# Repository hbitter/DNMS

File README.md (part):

## [English text below](#dnms-digital-noise-measurement-sensor-english)

## DNMS (Digital Noise Measurement Sensor)

Ein Sensor-Modul zur Schallpegelmessung. Es wird neben dem LAeq-Wert über einem Zeitintervall auch der min. und max. LA-Wert in diesem Zeitintervall festgehalten. Das zentrale Element des DNMS ist ein digitales MEMS-Mikrofon (InvenSense ICS-43434). Ein Mikrocontroller-Board (Teensy3.6 / Teensy4.0) übernimmt die digitalen Daten vom Mikrofon über die I²S Schnittstelle als  24-Bit, 44,1 kHz PCM Daten (ab Firmware Version 2 - zuvor nur 16-Bit).  Die Audiodaten werden über einen digitalen A-Filter bewertet, dann wird der Effektivwert bestimmt und daraus der Schalldruckpegel entsprechend der Mikrofonsensitivität berechnet. Die einzelnen Schalldruckpegelwerte werden zu einem fortlaufenden LAeq-Wert weitergerechnet. Ebenso werden der max. und min. Schalldruckpegel (LAmax, LAmin) aus dem Intervall abgespeichert.

Die Werte werden dann über eine I²C-Schnittstelle an einen abfragenden Mikrocontroller zur Weiterverarbeitung übertragen. Das Abfrage-Intervall kann 1 Sekunde betragen oder auch bis zu 3600 Sekunden.

Eine Version mit der Möglichkeit das Frequenzspektrum zu betrachten ist seit einiger Zeit verfügbar. Terzwerte von 20Hz - 20000Hz können ausgegeben werden. Terzwerte werden z.Zt. nicht von Sensor.Community unterstützt, deshalb gibt es spezielle Versionen der NodeMCU Firmware um Terzwerte auf der lokalen Webseite der NodeMCU auszugeben und an weitere APIs wie z.B. zu einer InfluxDB zu senden.

Mit der Firmware Version 5 für Teensy4.0 werden nun auch Z-Werte (LZeq, LZmin, LZmax sowie Z-Terzwerte) unterstützt.

### Bei der Firma Watterott electronic GmbH kann nun das Mikrofon IM72D128 von Infineon fertig in einem Kunststoffrohr eingegossen im Shop bestellt werden (https://shop.watterott.com/Mikrofon-IM72D128V01-im-127mm-Rundrohr). Das IM72D128 Mikrofon auf einer Platine und mit Anschlusskabel aber nicht  im Kunststoffrohr eingegossen ist ebenfalls verfügbar (https://shop.watterott.com/Mikrofon-IM72D128V01-Platine-mit-Anschlussleitung).
 
## Neuigkeiten

### Oktober 2026

- Neue Teensy4.0 Firmware DNMS_V6.0.x für IM72D128 und ICS-43434 Mikrofone.   
 	+ Komplettes Refactoring der Firmware mit Optimierung der Verwendung von Double (nur noch wenn absolut notwendig), dadurch erfordert die Berechnung der Leq Werte deutlich weniger Ressourcen.
 	+  Fehlerbeseitigung einer Race-Condition zwischen 1. und 2. Messintervall.
 	+  Die Parameterwerte zur Frequenzgangkorrektur sind nicht mehr in der Firmware fest abgespeichert. Es werden für jeden Mikrofontyp 31 Korrekturwerte vom Kommunikationsprozessor an die Teensy Firmware beim Start übertragen, daraus berechnet die Teensy Firmware die Korrekturwerte für den gewählten Mikrofontyp für die FFT Bins.
 	+  Änderung der Filterparameter für die I²C Kommunikation zwischen Teensy und Kommunikationsprozessor, dadurch stabilere I²C Übertragung. Beim Kompilieren der Firmware ist es deshalb notwendig die angepasste teensy4_i2c-master Library zu benutzen (zu finden unter Firmware/Teensy/Teensy4.0/).

 	<mark>Achtung: Um diese Firmware zu nutzen, ist die Firmware Version airrohr-DNMS-6.0.0 (oder höher) beim NodeMCU Kommunikationsprozessor oder beim Raspberry Pi  die Version dnms-0.9.27 bzw. dnms-0.9.28 (oder höher) notwendig. Nur diese Versionen haben die Parameter zur Frequenzgangkorrektur abgespeichert und übertragen diese Werte beim Start.<mark>
 	
- Neue NodeMCU Firmware AIRROHR-DNMS-6.0, AIRROHR-DNMS-6.0-en, AIRROHR-DNMS-6.0-fr
	+ Unterstützung der Teensy4.0 Firmware DNMS_V6.0.x mit der wesentlichen Änderung, dass die Frequenzgangkorrekturwerte beim Start von der NodeMCU an die Teensy4.0 Firmware übertragen werden. Ist eine ältere Firmware auf dem Tennsy4.0 Board installiert, so wird dies ebenfalls unterstützt d.h. es ist abwärtskompatibel.
	+ Neue Farbe und neues Logo für den lokalen Webserver:
	 
	+ Verbessertes Handling der Datenübertragung zu Sensor.Community und zu MQTT-Brokern um Datenverlust bei der Übertragung weiter zu reduzieren.
	
	+  Möglichkeit die NodeMCU Firmware direkt über den Webbrowser auf einen ESP8266  zu flashen. Dies ist möglich mit allen Webbrowsern, die das Web Serial API unterstützen (Chrome, Edge, Brave, Opera aber nicht Firefox ). Um die Funktion zu benutzen,  den entsprechenden Link aufrufen abhängig von der gewünschten Sprachversion:	
		+ Webflasher Deutsche Firmware: https://hbitter.github.io/DNMS/flash-de.html
		+ Webflasher Englische Firmware: https://hbitter.github.io/DNMS/flash-en.html
		+ Webflasher Französische Firmware: https://hbitter.github.io/DNMS/flash-fr.html

- Raspberry Pi Firmware Versionen dnms-0.9.27 und dnms-0.9.28
	+ Die Version dnms-0.9.28 enthält  im Unterschied zur Version dnms-0.9.27 einen lokalen Webserver, der Sztatus Informationen anzeigt und über den die Konfiguration des Sensors angesehen und geändert werden kann. Weiterhin bietet die Version dnms-0.9.28 ein HTTP API (POST) für die Daten des 1. Messintervalls.
	+ Unterstützung der Teensy4.0 Firmware DNMS_V6.0.x mit der wesentlichen Änderung, dass die Frequenzgangkorrekturwerte beim Start vom Raspberry Pi  an die Teensy4.0 Firmware übertragen werden. Ist eine ältere Firmware auf dem Tennsy4.0 Board installiert, so wird dies ebenfalls unterstützt d.h. es ist abwärtskompatibel.
	+ Lokaler Webserver der Version dnms-0.9.28 mit Farbe und Logo entsprechend der NodeMCU Version.

### Mai 2026

- Neues Teensy 4.0 Board DNMS-T4.0-V1.8S mit Layout für SMD Bestückung , so dass nicht nur die Herstellung der Platine beauftragt werden kann sondern direkt die Bestückung bei Firmen wie Aisler, EuroCircuits, JLCPCB oder PCBWay und weiteren. Das Einlöten des Teensy Boards sollte aus Kosten- und Logistikgründen allerdings weiterhin selbst erfolgen. Zwei Bauteilelisten sind als Beispiel für die Bestellung fertig bestückter Boards beigefügt. Dies ist jedoch immer den aktuell lieferbaren Bauelementen anzupassen. Das Layout basiert auf der EasyEDA Vorlage von Ralf Bötticher (vielen Dank!). Weiterhin gibt es zwei Änderungen im Layout:
	+ Verzicht der Brücke J1,  die Brücke war zur Stromversorgung für das standalone Flashen des Boards. Eine Auftrennung der Verbindung VIN - VUSB auf dem Teensy 4.0 Board ist nicht mehr notwendig.
	+ Einfügung einer Sicherung F1 in die 5V Versorgungsleitung der extended I²C Verbindung d.h. zwischen Kommunikationsprozessor und Teensy 4.0 Board.

 - Neue Raspberry Pi Firmware dnms-0.9.25 mit folgenden Verbesserungen:
	+ Möglichkeit C-Werte abzufragen und weiterzugeben, dazu ist die Teensy 4.0 Version DNMS_V5.9.x Voraussetzung. Abhängig von der Menge der übertragenen Daten zwischen Teensy und Raspberry Pi  wird empfohlen die I²C Übertragungsrate von 100 kHz auf 200 kHz zu erhöhen (`dtparam=i2c_arm=on,i2c_arm_baudrate=20000` in der Datei `/boot/firmware/config.txt`).
	+ In der Konfigurationsdatei dnms.conf können nun wieder die Bool Werte mit true und false angegeben werden.

- Neue Teensy 4.0 Firmware DNMS_V5.9.x  für IM72D128 und ICS-43434 Mikrofone mit dem Unterschied zur Version DNMS_V5.8.x, dass zusätzlich C-Werte berechnet und abgerufen werden können. Wenn keine C-Werte benötigt werden, ist die Version  DNMS_V5.8.x weiterhin aktuell. Eine Version mit Abfrage der C-Werte ist die Raspberry Pi Version dnms-0.9.25. Eine Abfrage der C-Werte für die NodeMCU Firmware ist z.Zt. nicht geplant.

- Neue NodeMCU Firmware AIRROHR-DNMS-5.17, AIRROHR-DNMS-5.17-en, AIRROHR-DNMS-5.17-fr
	+ Neue Konfigurationsmöglichkeit für verschiedene Mikrofone und Frequenzgangkorrekturen der Mikrofone. Eine Teensy4.0 Version ab DNMS_V5.8.x ist Voraussetzung um dies zu nutzen.
	+ Konfiguration eines digitalen Eingangs an der der NodeMCU. Der Zustand wird mit der Bezeichnung  DIN01 zur InfluxDB übertragen.
	+ Kleine Korrekturen im Source Code, so dass in der Arduino IDE Version 2.3.8 die Übersetzung ohne Warnungen erfolgt.

- Neue Teensy 4.0 Firmware DNMS_V5.8.x  für IM72D128 und ICS-43434 Mikrofone mit:
	+ zusätzlicher Auswahl der Frequenzgangkorrektur für das DLR Gehäuse mit IM72D128 Mikrofon, sowie Auswahl ohne Frequenzgangkorrektur für IM72D128 und ICS-43434 Mikrofon.
	+ Kleine Korrekturen im Source Code, so dass in der Arduino IDE Version 2.3.8 die Übersetzung ohne Warnungen erfolgt. Dies betrifft auch die Library dnms_audio_lib-master.zip, deshalb beim Übersetzen die veränderte Library einbinden.
	+ Korrekturen an der I²C Übertragung, Änderung der Werte für die Glitch Filter von SDA und SCL im Slave Modus. Diese Korrekturen befinden sich in der Library  teensy4_i2c-master.zip, deshalb beim Übersetzen die veränderte Library einbinden.

### Mai 2025

- Neues Testprogramm für Teensy4.0 Board und angeschlossenem Mikrofon ICS-43434:  DNMS_Vt.8.4 und für Mikrofon IM72D128: DNMS_Vt.8.6, mit verbesserter Frequenzgangkorrektur

- Neue Teensy 4.0 Firmware DNMS_V5.5.x  für IM72D128 und ICS-43434 Mikrofone mit:
	+ Verbesserte Korrektur des Frequenzgangs für IM72D128 Mikrofon und ICS-43434 Mikrofon. Dies verbessert auch die Terzwerte des Spektrums.

 - Neue Raspberry Pi Firmware dnms-0.9.23 ersetzt dnms-0.9.21 aufgrund von Fehlern:
	 + Bei der Umwandlung der MAC-Adresse in die ID
	 + Entfernung Testausgabe der Daten auf Konsole bei Sensor.Community Übertragung
	 + Beseitigung Pufferüberlauf für InfluxDB/MQTT Übertragung, wenn keine Übertragung konfiguriert war

### Oktober 2024

- Neue NodeMCU Firmware AIRROHR-DNMS-5.16 mit:
	+ Neue Konfigurationsmöglichkeit die WLAN Verbindung ohne Passwort auszuwählen aufgrund einer Änderung in der Wifi Lib. Dies ist notwendig  z.B. für Freifunk WLAN Verbindungen.
	+ Verbesserte Fehlerbehandlung bei der Datenübertragung und entsprechende Fehlerausgaben.
	+ Fehlerbeseitigung bei der Übertragung des Zeitstempels zur InfluxDB und zu einem MQTT Broker, wenn der DNMS Sensor nicht konfiguriert ist.

### September 2024

 - Raspberry Pi dnms-0.9.21 ersetzt Version dnms-0.9.20 aufgrund von Fehlern.
 	+ Fehler in der dnms.conf beim Eintrag 'mqtt_transmit'.
 	+ Fehlerhaft gesetzte Prioritäten für die Threads in der dnms.conf ('prio_1st_timer', ... usw).
 	+ Neben der InfluxDB HTTP Übertragung kann nun parallel eine Übertragung der Werte zu einem MQTT Broker erfolgen.
 		
 - Raspberry Pi dnms-0.9.20 Version mit folgenden neuen Funktionen:
	+ Data Logging der Messwerte auf der SD-Karte des Raspberry Pi
	+ Externer Start und Stop der Messwertübertragung, Ausgabe und Speicherung mittels einer named pipe
	+ Änderung der Eingabe von Bool-Werten in der Konfigurationsdatei dnms.conf: Für false eine '0' und für true eine '1' eingeben.

 - Möglichkeit die NodeMCU Firmware direkt über den Webbrowser auf einen ESP8266  zu flashen. Dies ist möglich mit allen Webbrowsern, die das Web Serial API unterstützen (Chrome, Edge, Brave, Opera aber nicht Firefox ). Um die Funktion zu benutzen,  den entsprechenden Link aufrufen abhängig von der gewünschten Sprachversion:
	+ Deutsche Firmware: https://hbitter.github.io/DNMS/flash-de.html
	+ Englische Firmware: https://hbitter.github.io/DNMS/flash-en.html
	+ Französische Firmware: https://hbitter.github.io/DNMS/flash-fr.html

### Juli 2024

- Neue Firmware für Teensy4.0 DNMS_V5.4.x - für ICS-43434 und IM72D128 Mikrofon
	+ Ersetzt DNMS_V5.3.x da in der Version DNMS_V5.3.x Fehler in der Berechnung der Terzwerte waren. DNMS_V5.3.x bitte ersetzen mit DNMS_V5.4.x 
	
- Neue NodeMCU Firmware AIRROHR-DNMS-5.12 mit:
	+ NTP Server können nun in der Konfiguration gesetzt werden unter "Weitere Einstellungen"
	+ Konfigurationsänderung für die Übertragung zum MQTT Broker, eigenes Feld für die Konfiguration der MQTT Messung. Dies wird im InfluxDB Line Protocol als Measurement weitergegeben

 - Raspberry Pi dnms-0.9.18 Fehlerkorrektur und neue Funktion:
	 - Korrektur eines Fehlers: Wenn nur die Ausgabe auf dem Terminal konfiguriert war, wurden die Werte nicht richtig auf dem Terminal ausgegeben.
 	- Neue Möglichkeit der Weitergabe von Messwerten mittels einer named pipe (oder auch fifo) zu anderen Anwendungen auf dem Raspberry Pi.

### Juni 2024

 - Raspberry Pi dnms-0.9.16 Korrektur der Versionsnummer:
	 - Die Versionsnummer wurde falsch (0.9.15 statt 0.9.16) angezeigt
 - Neue NodeMCU Firmware AIRROHR-DNMS-5.8 mit:
	 - MQTT Übertragung (z.Zt. kein TLS)
	 - Unterstützung der neuen Teensy4.0 Firmware DNMS_V5.3.x (Mikrofone ICS-43434 und IM72D128 in einer Teensy4 Firmware)
	 - Möglichkeit nach Restart mit den Messungen zur vollen Minute oder zur vollen Stunde zu beginnen<br>
	 
	 Weitere Details dazu im README.md unter Firmware/NodeMCU.

 - Erweiterte Raspberry Pi Anwendung dnms-0.9.16 mit:
	 - MQTT Übertragung zu einem MQTT-Broker (z.Zt. kein TLS)
	 - Unterstützung der neuen Teensy4.0 Firmware DNMS_V5.3.x (Mikrofone ICS-43434 und IM72D128 in einer Teensy4 Firmware)
	 - Einführung eines DNMS Korrekturwertes für die Lärmwerte (nicht für Frequenzspektren) entsprechend der NodeMCU Firmware  <br>
	 
	 Weitere Details dazu im README.md unter Firmware/Raspberry Pi.
	 
 - Neue Teensy4.0 Firmware DNMS_V5.3.x mit:
	 - Zusammenführung der bisher getrennten Versionen für die beiden Mikrofone ICS-43434 und IM72D128 in einer Teensy4.0 Firmware. Die Auswahl des Mikrofons erfolgt über die Konfiguration in der NodeMCU bzw. im Raspberry Pi und wird mittels Umschaltbefehl an die Teensy4.0 Firmware übertragen. Wird kein Umschaltbefehl übertragen ist als standardmäßig das ICS-43434 ausgewählt d.h. auch ältere NodeMCU Firmware unterstützt die Version DNMS_V5.3.x mit ICS-43434 Mikrofon. <br>

	 Weitere Details dazu im README.md unter Firmware/Teensy4.0/V5.	 

### April 2024
 - Neue NodeMCU Firmware NRZ-2020-134-DNMS-5.6 mit:
	 - Fehlerbeseitigung für DNMS Korrekturwert (Issue #54)
	 - LED Statusanzeige
	 - geänderte Speicheraufteilung<br>
	 
	 Weitere Details dazu im README.md unter Firmware/NodeMCU.

### Februar 2024
   - Verbesserte Teensy4.0 Firmware für die Mikrofone ICS-43434 und IM72D128 mit verbessertem internen Zeitverhalten (Upgrade empfohlen): 
     - DNMS_V5.2.4 - für ICS43434 mit Teensy4.0
     - DNMS_V5.2.6 - für IM72D128 mit Teensy4.0
 	
  - Standalone Testprogramme für Teensy4.0 und die Mikrofone ICS-43434 und IM72D128 mit verbessertem internen Zeitverhalten	und geänderter Ein- und Ausgabe beim Start, es können Messintervall ab 125ms eingestellt werden, die Ausgabe von Terzwerten ist ab 500ms möglich:
 	- DNMS_Vt.7.4 - für ICS43434 mit Teensy4.0
 	- DNMS_Vt.7.6 - für IM72D128 mit Teensy4.0
  
  - dnms-0.9.12 erste Version der Raspberry Pi Anwendung um den DNMS Sensor auszulesen und Daten an Sensor.Community und/oder zu einer InfluxDB zu senden als Alternative zu einer NodeMCU (Airrohr-Board). Die Raspberry Pi Anwenung unterstützt zur Übertragung an eine InfluxDB zwei zeitlich unterschiedliche Messintervalle mit unterschiedlich konfigurierbaren Messwerten. Die Messwerte des 2. Messintervalls werden erst ab der Überschreitung eines Schwellwertes (LAeq) übertragen.  
  - KiCad Layouts an KiCad Version 7 angepasst für die folgenden PCBs (im Layout selbst keine Änderung):
	  + DNMS-T4.0-V1.7
	  + DNMS-RPI-HAT-V1.0
	  + IM72D128-PCB-V1.0
	  + IM72D128-Tube-PCB-V1.0

### September 2023
  - Neue NodeMCU Firmware NRZ-2020-134-DNMS-5.4 auch in englischer und französischer Version mit:
    - Verbesserungen bei der Fehlerausgabe von Übertragungen zu Sensor.Community und zu einer InfluxDB
    - Vergrößerung des Übertagungspuffers, so dass neben sämtlichen DNMS Werten auch die Werte weiterer Sensoren zu einer InfluxDB übertragen werden können.
    - Link zur Meldung von Problemen geändert auf https://github.com/hbitter/DNMS/issues 

### August 2023
 - Standalone Testprogramme für Teensy4.0 und die Mikrofone ICS-43434 und IM72D128:
 	- DNMS_Vt.5.4 - für ICS43434 mit Teensy4.0
 	- DNMS_Vt.5.6 - für IM72D128 mit Teensy4.0
 
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
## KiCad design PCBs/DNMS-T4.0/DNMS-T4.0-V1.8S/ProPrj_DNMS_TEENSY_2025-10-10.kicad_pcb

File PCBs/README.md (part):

## [English text below](#pcbs-english)

## PCBs

## Funktion der verschiedenen PCBs

### IM72D128 Mikrofon PCBs
Das IM72D128 Mikrofon benötigt zwei PCBs: Ein rundes Mikrofon Board, auf dem neben dem IM72D128 noch ein Widerstand und ein Kondensator montiert sind. Ein zweites längliches Board, dass in ein 1/2" Rohr zusammen mit dem Mikrofon eingebaut (eingegossen) wird, ist für die Umsetzung der PDM Schnittstelle des Mikrofons auf die I²S Schnittstelle des DNMS Teensy4.0 Boards notwendig. Dadurch wird die Anschlusskompatibilität zum ICS-43434 bewahrt.
PCB Versions Historie:
- IM72D128-PCB-V1.0 - erste veröffentlichte Version rundes Mikrofon Board
- IM72D128-Tube-PCB-V1.0 - erste veröffentlichte Version längliches Interface Board

<br>
<br>

### ICS-43434 Mikrofon PCB
Ein rundes Mikrofon Board, das in ein 1/2" Plastikrohr (oder in 13mm Edelstahlrohr mit 12mm Innendurchmesser) eingebaut werden kann. Auf dem Board ist eine JST SH Buchse, auf die ein Kabel mit JST SH Stecker aufgesteckt werden kann. Entsprechende Kabel sind z.B. bei [Aliexpress hier erhältlich](https://de.aliexpress.com/item/33013143346.html?spm=a2g0s.9042311.0.0.b4924c4dbhEWkt).

PCB Versions Historie:
- ICS-43434-PCB-V1.3 - erste veröffentlichte Version
- ICS-43434-PCB-V1.4 - Durchmesser für die akustische Öffnung geändert con 0,6mm auf 0,7mm

<br>

### Airrohr PCB
Basis Board für eine NodeMCU V2 od. V3 mit Anschlüssen für die folgenden Sensoren:
- Feinstaubsensor SDS011 über Steckverbinder
- Feinstaubsensor SPS30 (Sensirion) über Steckverbinder
- DHT22 Temperatur- Feuchtigkeitssensor über Stiftleiste
- I²C Anschlüsse mit 3,3V und 5V Versorgungsspannungs für DNMS und andere Sensoren (z.B. BMP/E280 Temperatur- Feuchtigkeitssensor) über Stiftleiste
- I²C-Bus-Verlängerung mit 5V Versorgungsspannung für entfernten DNMS Sensor (bei Verbindungen > 250mm) über RJ12 Buchse bzw. Stiftleiste

PCB Versions Historie:
- Airrohr-V1.1 - erste Version
- Airrohr-V1.2 - I²C-Bus Verlängerung mit zusätzlicher RJ-12 (Modular Jack) 6P/6C Buchse
- Airrohr-V1.4 - RJ12 Buchse nun für zwei unterschiedliche "Footprints" und in der Ausrichtung geändert 
			   - einige Bauelemente nach innen verschoben, damit der Einbau in ein Gehäuse (Rohr) einfacher ist 
			   - P82B715 (I²C-bus Extender IC) kann im DIP8 Gehäuse oder im SO8 Gehäuse bestückt werden
- Airrohr-V1.5 - Masseflächen an Ober- und Unterseite
- Airrohr-V1.6 - Layoutänderung der Stromversorgung an den Bauteilen R1, R2, R3 und J4

<br>

### DNMS-RPI-HAT
Aufsatzboard für den Raspberry Pi um einen DNMS Sensor und andere I²C Sensoren mit dem Raspberry Pi zu verbinden. Das Board hat die gleich Größe wie ein RPI Zero W. Die folgenden Anschlüsse sind vorhanden:
- I²C-Bus Verlängerung mit 5V Versorgungsspannung für einen DNMS Sensor und Kabellängen > 250mm mittels RJ12 (Modular Jack) 6P/6C Buchse
- Feinstaubsensor SPS30 (Sensirion) mittels JST ZH Buchse
- 2 x I²C Anschlüsse über Stiftleiste mit 3,3V Versorgungsspannung für weitere Sensoren

PCB Versions Historie:
- DNMS-RPI-HAT-V1.0 - erste Version

<br>

### DNMS-T3.6+NodeMCU
Kombiniertes Board für DNMS mit Teensy3.6 und NodeMCU V2 od. V3, neben der DNMS Funktion sind noch Anschlüsse für die die folgenden Sensoren vorhanden:
- Feinstaubsensor SPS30 (Sensirion) über Steckverbiner
- I²C Anschluss mit 3,3V Versorgungsspannung für z.B. BMP/E280 Temperatur- Feuchtigkeitssensor od. SHT3X Sensor über Stiftleiste

PCB Versions Historie:
- DNMS-T3.6+NodeMCU V1.0 - erste Version

### DNMS-T3.6
Basis Board für Teensy3.6 zum Anschluss ICS-43434 Mikrofon, die Lärmwerte werden über I²C an einen Kommunikationsprozessor (z.B. Airrohr-V1.4 mit NodeMCU) übertragen, für Entfernungen zum Kommunikationsprozessor > 250mm ist eine optionale I²C-Bus-Verlängerung vorhanden. Ein standard Telefonkabel mit RJ12 Verbindern (6P/6C) dient dann zur Verbindung des DNMS mit dem Airrohr Board.

PCB Versions Historie:
- DNMS-T3.6-V1.1 - erste Version
- DNMS-T3.6-V1.2 - I²C-Bus-Verlängerung mit zusätzlicher RJ-12 (Modular Jack) 6P/6C Buchse (passend zum Airrohr-V1.2)
- DNMS-T3.6-V1.3 - P82B715 (I²C-bus Extender IC) kann im DIP8 Gehäuse oder im SO8 Gehäuse bestückt werden
- DNMS-T3.6-V1.4 - RJ12 Buchse nun für zwei unterschiedliche "Footprints"

### DNMS-T4.0+NodeMCU
Kombiniertes Board für DNMS mit Teensy4.0 und NodeMCU V2 od. V3, neben der DNMS Funktion sind noch Anschlüsse für die die folgenden Sensoren vorhanden:
- Feinstaubsensor SPS30 (Sensirion) über Steckverbiner
- I²C Anschluss mit 3,3V Versorgungsspannung für z.B. BMP/E280 Temperatur- Feuchtigkeitssensor od. SHT3X Sensor über Stiftleiste

PCB Versions Historie:
- DNMS-T4.0+NodeMCU V1.2 - erste veröffentlichte Version
- DNMS-T4.0+NodeMCU V1.4 - einige Bauelemente wurden nach innen verschoben, damit der Einbau ins Gehäuse einfacher wird
- DNMS-T4.0+NodeMCU V1.5 - Masseflächen auf der Ober- und Unterseite um die Abschirmung zwischen Teensy4.0 und WLAN der NodeMCU zu erhöhen

<br>

### DNMS-T4.0
Basis Board für Teensy4.0 zum Anschluss ICS-43434 Mikrofon, die Lärmwerte werden über I²C an einen Kommunikationsprozessor (z.B. Airrohr-V1.4 mit NodeMCU) übertragen, für Entfernungen zum Kommunikationsprozessor > 250mm ist eine optionale I²C-Bus-Verlängerung vorhanden. Ein standard Telefonkabel mit RJ12 Verbindern (6P/6C) dient dann zur Verbindung des DNMS mit dem Airrohr Board.

PCB Versions Historie:
- DNMS-T4.0-V1.2 - erste Version
- DNMS-T4.0-V1.4 - P82B715 (I²C-bus Extender IC) kann im DIP8 Gehäuse oder im SO8 Gehäuse bestückt werden
				 - RJ12 Buchse für I²C-Bus-Verlängerung mit zwei unterschiedlichen "Footprints"
- DNMS-T4.0-V1.5 - Masseflächen an Ober- und Unterseite
- DNMS-T4.0-V1.7 - Zusätzliche JST SR/SZ Buchsen für die Verbindung zum Mikrofon, wahlweise für 1:1 Kabel (Bezeichnung straight auf der Unterseite) oder "verdrehte" Kabel (Bezeichnung reverse auf der Unterseite). Achtung: Das Löten dieser JST Buchsen ist nicht ganz einfach.

<br>

<br>

<br>

- DNMS-T4.0-V1.8S mit Layout für SMD Bestückung , so dass nicht nur die Herstellung der Platine beauftragt werden kann sondern direkt die Bestückung bei Firmen wie Aisler, EuroCircuits, JLCPCB oder PCBWay und weiteren. Das Einlöten des Teensy Boards sollte aus Kosten- und Logistikgründen allerdings weiterhin selbst erfolgen. Zwei Bauteilelisten sind als Beispiel für die Bestellung fertig bestückter Boards beigefügt. Dies ist jedoch immer den aktuell lieferbaren Bauelementen anzupassen. Das Layout basiert auf der EasyEDA Vorlage von Ralf Bötticher (vielen Dank!). Weiterhin gibt es zwei Änderungen im Layout:
	+ Verzicht der Brücke J1,  die Brücke war zur Stromversorgung für das standalone Flashen des Boards. Eine Auftrennung der Verbindung VIN - VUSB auf dem Teensy 4.0 Board ist nicht mehr notwendig.
	+ Einfügung einer Sicherung F1 in die 5V Versorgungsleitung der extended I²C Verbindung d.h. zwischen Kommunikationsprozessor und Teensy 4.0 Board.
	
<br>

----------------------------------------------------------------------------------------------------------------
## PCBs English

## What are the different PCBs for

### IM72D128 microphone PCBs
Using the IM72D128 microphone is done by a set of two PCBs. A small round PCB holding the microphone itself and in addition one resistor and one capacitor. A second longish PCB is used holding the necessary circuitry for converting the microphones PDM interface to the Teensy4.0 I²S interface. Thus  compatibility with the former ICS-43434 microphone is preserved. Both boards can be mounted in 1/2" tube and sealed with a compound.

PCB revision history:
- IM72D128-PCB-V1.0 - first version round microphone board on GitHub
- IM72D128-Tube-PCB-V1.0 - first version longish interface board on GitHub

<br>
<br>

### ICS-43434 microphone PCB
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
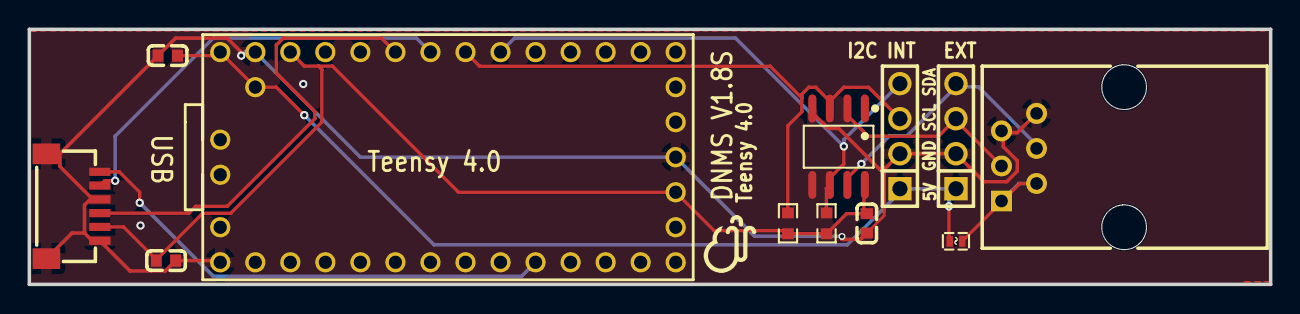
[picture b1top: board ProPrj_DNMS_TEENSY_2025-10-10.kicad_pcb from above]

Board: 2 copper layers, 90.0 x 18.5 mm, 12 parts (0 on the bottom side), 11 nets.

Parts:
ET1: C0603
F1: F0402
HB1: C0603
HFT1: SOIC-8_L4.9-W3.9-P1.27-LS6.0-BL
J2, J3: HDR-TH_4P-P2.54-V-M
MIC1: CONN-SMD_SM06B-SRSS-TB-LF-SN
R1, R2: R0603
RB1: C0603
RJ1: RJ11-TH_R-RJ11R06P-A000
U1: TEENSY4.0

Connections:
$1N32: F1.2, RJ1.1, RJ1.2
+3.3V: ET1.2, HFT1.8, MIC1.5, R1.2, R2.2, RB1.2, U1.16, U1.31
+5V: F1.1, HB1.2, J2.1, J3.1, U1.33, U1.34
GND: ET1.1, HB1.1, HFT1.4, J2.2, J3.2, MIC1.3, MIC1.6, MIC1.7, MIC1.8, RB1.1, RJ1.5, RJ1.6, U1.1, U1.17, U1.32
SCK: MIC1.4, U1.28
SCL: HFT1.3, J2.3, R2.1, U1.26
SCL_EX: HFT1.2, J3.3, RJ1.3
SD: MIC1.1, U1.10
SDA: HFT1.6, J2.4, R1.1, U1.25
SDA_EX: HFT1.7, J3.4, RJ1.4
WS: MIC1.2, U1.27

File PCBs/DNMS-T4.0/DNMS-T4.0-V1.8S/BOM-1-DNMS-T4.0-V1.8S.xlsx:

Reference | Qty | Value | DNP | Exclude from BOM | Exclude from Board | Footprint | Datasheet
ET1,HB1,RB1 | 3 | 100nF |  |  |  | Capacitor_SMD:C_0201_0603Metric
F1 | 1 | BSMD0402L-035 |  |  |  | Fuse:Fuse_0402_1005Metric
HFT1 | 1 | P82B715DR |  |  |  | Package_SO:SOIC-8_3.9x4.9mm_P1.27mm
J2,J3 | 2 | HX PZ2.54-1X4P ZZ |  |  |  | Connector_PinHeader_2.54mm:PinHeader_1x04_P2.54mm_Vertical
MIC1 | 1 | SM06B-SRSS-TB(LF)(SN) |  |  |  | ProPrj_DNMS_TEENSY_2025-10-10:CONN-SMD_SM06B-SRSS-TB-LF-SN
R1,R2 | 2 | 4.7k |  |  |  | Resistor_SMD:R_0201_0603Metric
RJ1 | 1 | R-RJ11R06P-A000 |  |  |  | ProPrj_DNMS_TEENSY_2025-10-10:RJ11-TH_R-RJ11R06P-A000
U1 | 1 | teensy4.0 |  |  |  | ProPrj_DNMS_TEENSY_2025-10-10:TEENSY4.0

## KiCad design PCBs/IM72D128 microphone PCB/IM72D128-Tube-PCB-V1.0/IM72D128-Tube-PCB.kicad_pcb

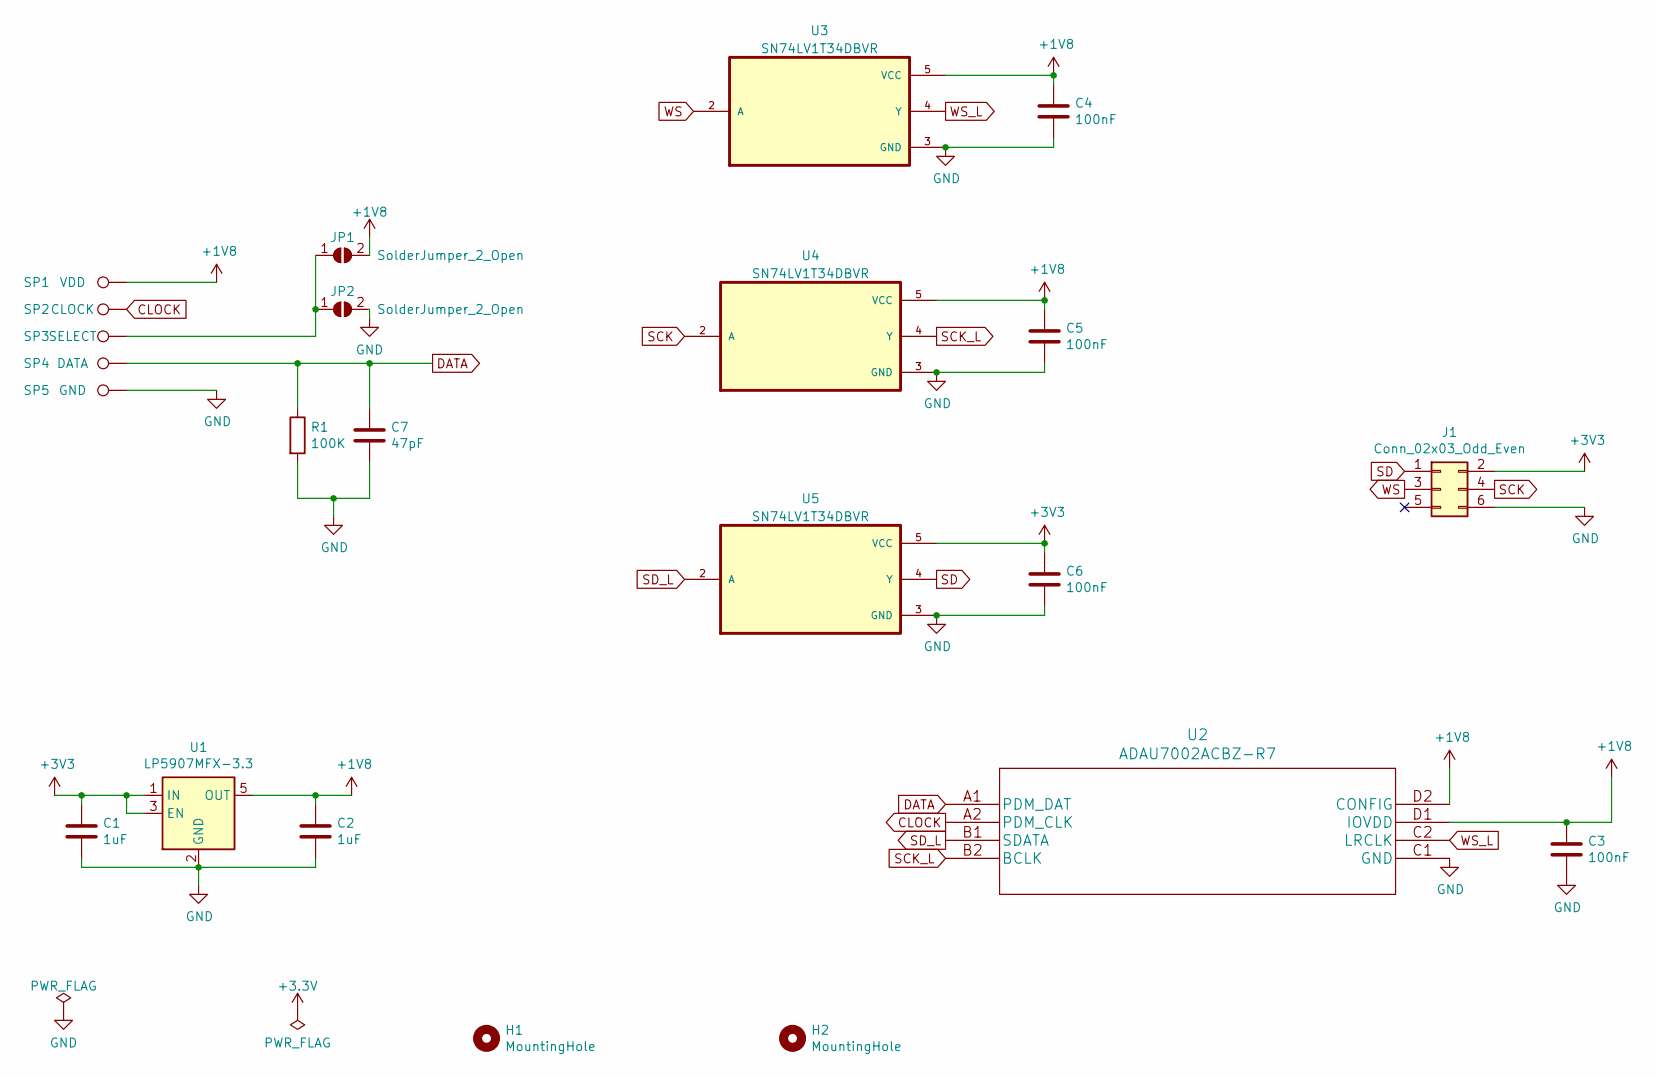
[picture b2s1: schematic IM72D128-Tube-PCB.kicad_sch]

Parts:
C1, C2: 1uF; C_0603_1608Metric
C3, C4, C5, C6: 100nF; C_0603_1608Metric
C7: 47pF; C_0603_1608Metric
H1, H2: MountingHole; MountingHole_2.1mm
J1: Conn_02x03_Odd_Even; PinHeader_2x03_P2.54mm_Vertical
JP1, JP2: SolderJumper_2_Open; SolderJumper-2_P1.3mm_Open_TrianglePad1.0x1.5mm
R1: 100K; R_0603_1608Metric
SP1: VDD; Solder_Pad_1.0x2.0mm
SP2: CLOCK; Solder_Pad_1.0x2.0mm
SP3: SELECT; Solder_Pad_1.0x2.0mm
SP4: DATA; Solder_Pad_1.0x2.0mm
SP5: GND; Solder_Pad_1.0x2.0mm
U1: LP5907MFX-3.3; SOT-23-5
U2: ADAU7002ACBZ-R7; ADAU7002
U3, U4, U5: SN74LV1T34DBVR; SOT95P280X145-5N

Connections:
+1V8: C2.1, C3.1, C4.1, C5.1, JP1.2 (B), SP1.1, U1.5 (OUT), U2.D1 (IOVDD), U2.D2 (CONFIG), U3.5 (VCC), U4.5 (VCC)
+3V3: C1.1, C6.1, J1.2, U1.1 (IN), U1.3 (EN), U5.5 (VCC)
CLOCK: SP2.1, U2.A2 (PDM_CLK)
DATA: C7.1, R1.1, SP4.1, U2.A1 (PDM_DAT)
GND: C1.2, C2.2, C3.2, C4.2, C5.2, C6.2, C7.2, J1.6, JP2.2 (B), R1.2, SP5.1, U1.2 (GND), U2.C1 (GND), U3.3 (GND), U4.3 (GND), U5.3 (GND)
unnamed: JP1.1 (A), JP2.1 (A), SP3.1
SCK: J1.4, U4.2 (A)
SCK_L: U2.B2 (BCLK), U4.4 (Y)
SD: J1.1, U5.4 (Y)
SD_L: U2.B1 (SDATA), U5.2 (A)
WS: J1.3, U3.2 (A)
WS_L: U2.C2 (LRCLK), U3.4 (Y)

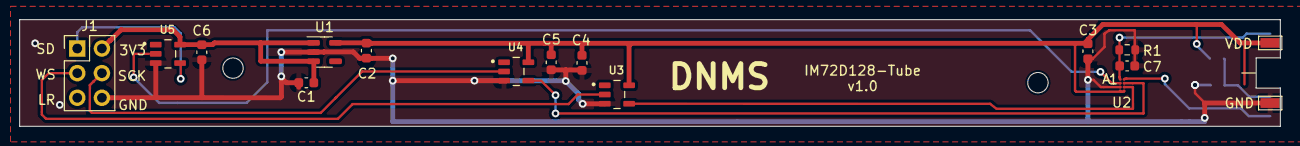
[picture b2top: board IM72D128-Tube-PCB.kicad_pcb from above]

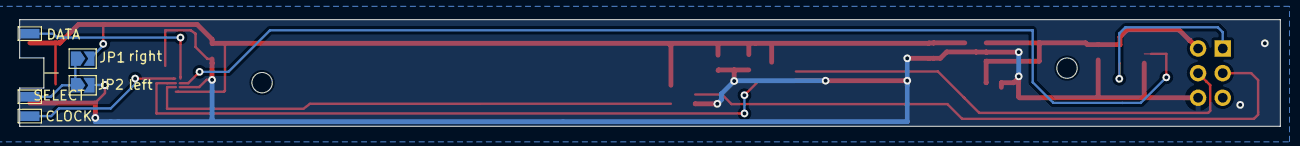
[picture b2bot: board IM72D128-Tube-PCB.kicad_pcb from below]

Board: 2 copper layers, 130.0 x 11.0 mm, 23 parts (5 on the bottom side), 12 nets.

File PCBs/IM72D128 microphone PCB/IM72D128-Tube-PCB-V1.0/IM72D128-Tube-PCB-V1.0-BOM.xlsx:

BOM | IM72D128-Tube-PCB |  | PCB Order: |  | Product No.:
Item # | *Designator | *Qty | Manufacturer | *Mfg Part # | Description / Value | *Package/Footprint | Type | Your Instructions / Notes
1 | C1, C2 | 2 | Samsung Electro-Mechanics | CL10A105KO8NNNC | 16V 1uF X5R ±10% 0603 Multilayer Ceramic Capacitors MLCC - SMD/SMT ROHS | 0603 | SMD | any other Manufacturer is ok
 | C3, C4, C5, C6 | 4 | Samsung Electro-Mechanics | CL10B104KO8NNNC | 16V 100nF X7R ±10% 0603 Multilayer Ceramic Capacitors MLCC - SMD/SMT ROHS | 0603 | SMD | any other Manufacturer is ok
 | C7 | 1 | Yageo | CC0603JRNPO8BN470 | 25V 47pF NP0 ±5% 0603 Multilayer Ceramic Capacitors MLCC - SMD/SMT ROHS | 0603 | SMD | any other Manufacturer is ok
 | R1 | 1 | Yageo | RC0603FR-07100KL | 100mW Thick Film Resistors 75V ±100ppm/℃ ±1% -55℃~+155℃ 100kΩ 0603 Chip Resisto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 | 0603 | SMD | any other Manufacturer is ok
 | U1 | 1 | Texas Instruments | LP5907MFX-3.3/NOPB | Fixed 1 250mA Positive 250mV@(250mA) 5.5V 90dB@(100Hz),60dB@(100kHz) 3.3V~3.3V 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 | SOT-23-5 | SMD
 | U2 | 1 | Analog Devices | ADAU7002ACBZ-R7 | 1.62V~3.6V WLCSP-8 Audio Interface ICs ROHS | WLCSP-8 | SMD
 | U3, U4, U5 | 3 | Texas Instruments | SN74LV1T34DBVR | Push Pull 8mA 1.6V~5.5V 8mA -40℃~+125℃ SOT-23-5 Buffer/Driver/Transceiver ROHS | SOT-23-5 | SMD

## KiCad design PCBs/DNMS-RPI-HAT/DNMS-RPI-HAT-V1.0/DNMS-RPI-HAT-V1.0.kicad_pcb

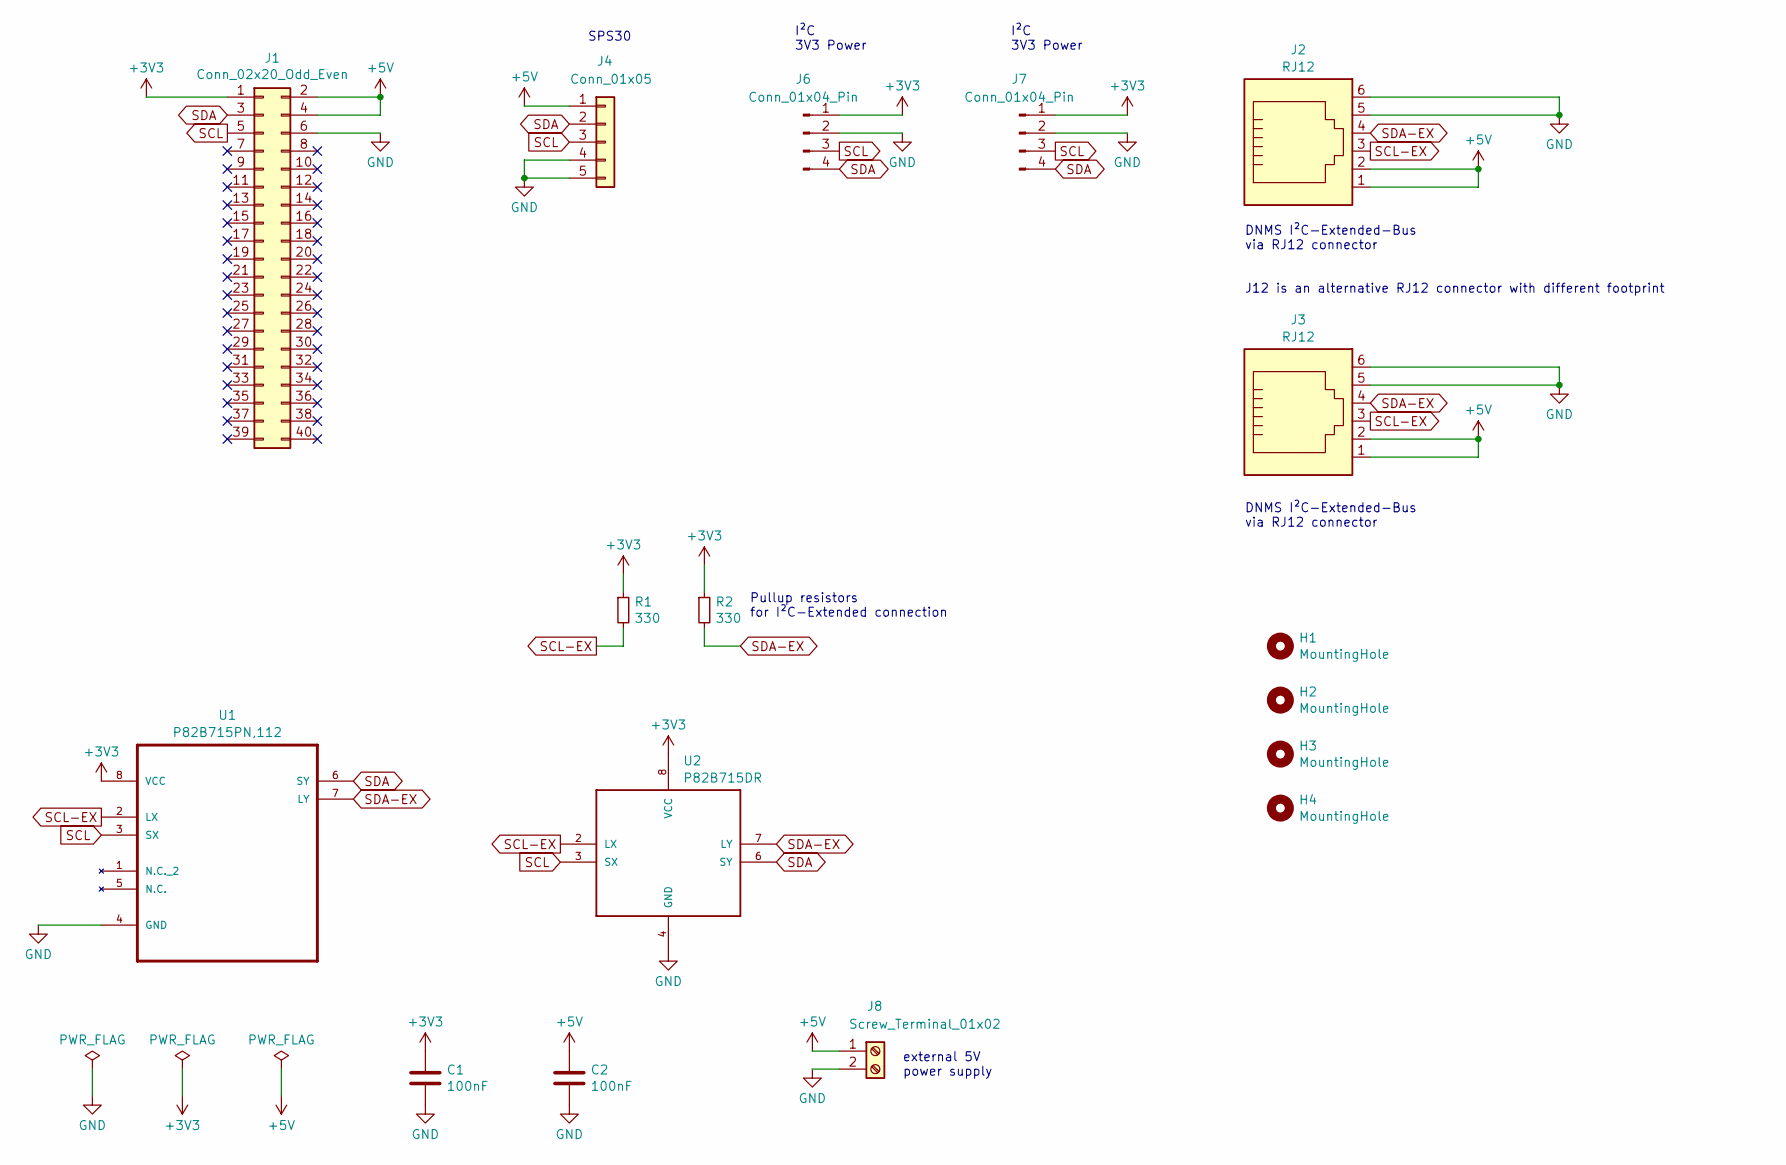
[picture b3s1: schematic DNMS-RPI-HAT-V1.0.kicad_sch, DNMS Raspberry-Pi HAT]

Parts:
C1, C2: 100nF; C_THT_100nF_L9.0mm_W2.0mm_P5.00mm_P7.50mm
H1, H2, H3, H4: MountingHole; MountingHole_2.7mm_M2.5_uHAT_RPi
J1: Conn_02x20_Odd_Even; PinSocket_2x20_P2.54mm_Vertical_Centered_Anchor
J2: RJ12; 54601906WPLF
J3: RJ12; E5566Q0LK22L
J4: Conn_01x05; JST_ZH_S5B-EH_1x05_P1.50mm_Horizontal
J6, J7: Conn_01x04_Pin; PinHeader_1x04_P2.54mm_Vertical
J8: Screw_Terminal_01x02; TerminalBlock_1x02_P2,54mm_P5.08mm_Horizontal
R1, R2: 330; R_Axial_DIN0207_L6.3mm_D2.5mm_P10.16mm_Horizontal
U1: P82B715PN,112; P82B715 DIP8
U2: P82B715DR; SOIC8

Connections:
+3V3: C1.1, J1.1, J6.1, J7.1, R1.1, R2.1, U1.8 (VCC), U2.8 (VCC)
+5V: C2.1, J1.2, J1.4, J2.1, J2.2, J3.1, J3.2, J4.1, J8.1
GND: C1.2, C2.2, J1.6, J2.5, J2.6, J3.5, J3.6, J4.4, J4.5, J6.2, J7.2, J8.2, U1.4 (GND), U2.4 (GND)
SCL: J1.5, J4.3, J6.3, J7.3, U1.3 (SX), U2.3 (SX)
SCL-EX: J2.3, J3.3, R1.2, U1.2 (LX), U2.2 (LX)
SDA: J1.3, J4.2, J6.4, J7.4, U1.6 (SY), U2.6 (SY)
SDA-EX: J2.4, J3.4, R2.2, U1.7 (LY), U2.7 (LY)

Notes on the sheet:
I²C 3V3 Power
DNMS I²C-Extended-Bus via RJ12 connector J12 is an alternative RJ12 connector with different footprint
DNMS I²C-Extended-Bus via RJ12 connector
external 5V power supply
Pullup resistors for I²C-Extended connection
SPS30

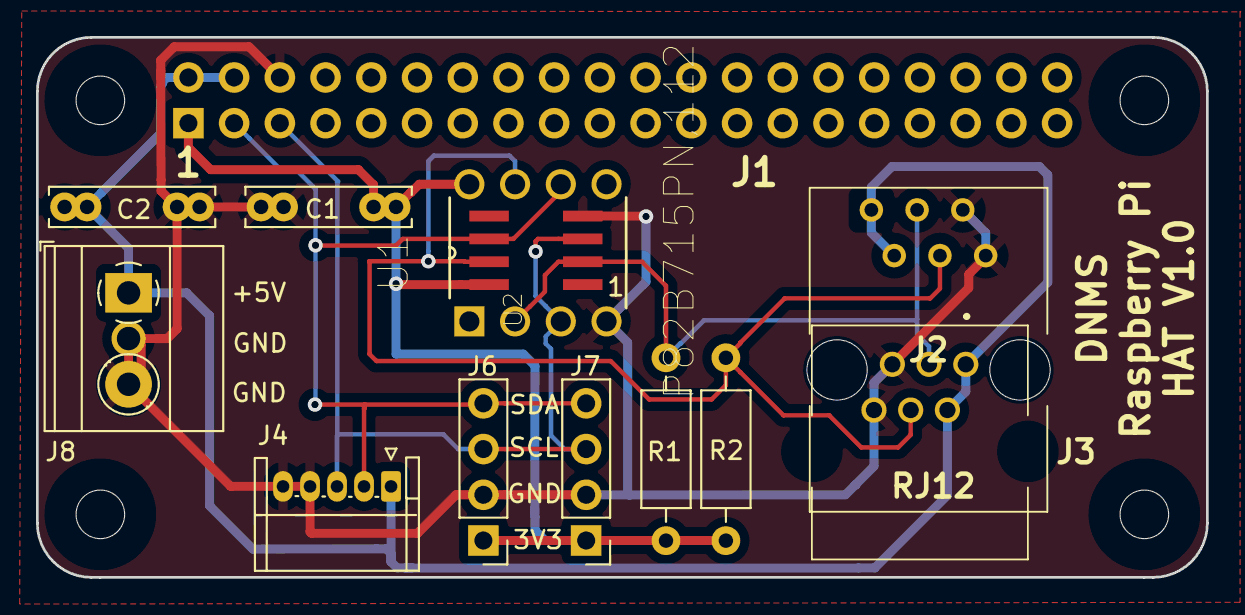
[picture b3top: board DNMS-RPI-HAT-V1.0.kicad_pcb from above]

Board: 2 copper layers, 65.0 x 30.0 mm, 17 parts (1 on the bottom side), 7 nets.

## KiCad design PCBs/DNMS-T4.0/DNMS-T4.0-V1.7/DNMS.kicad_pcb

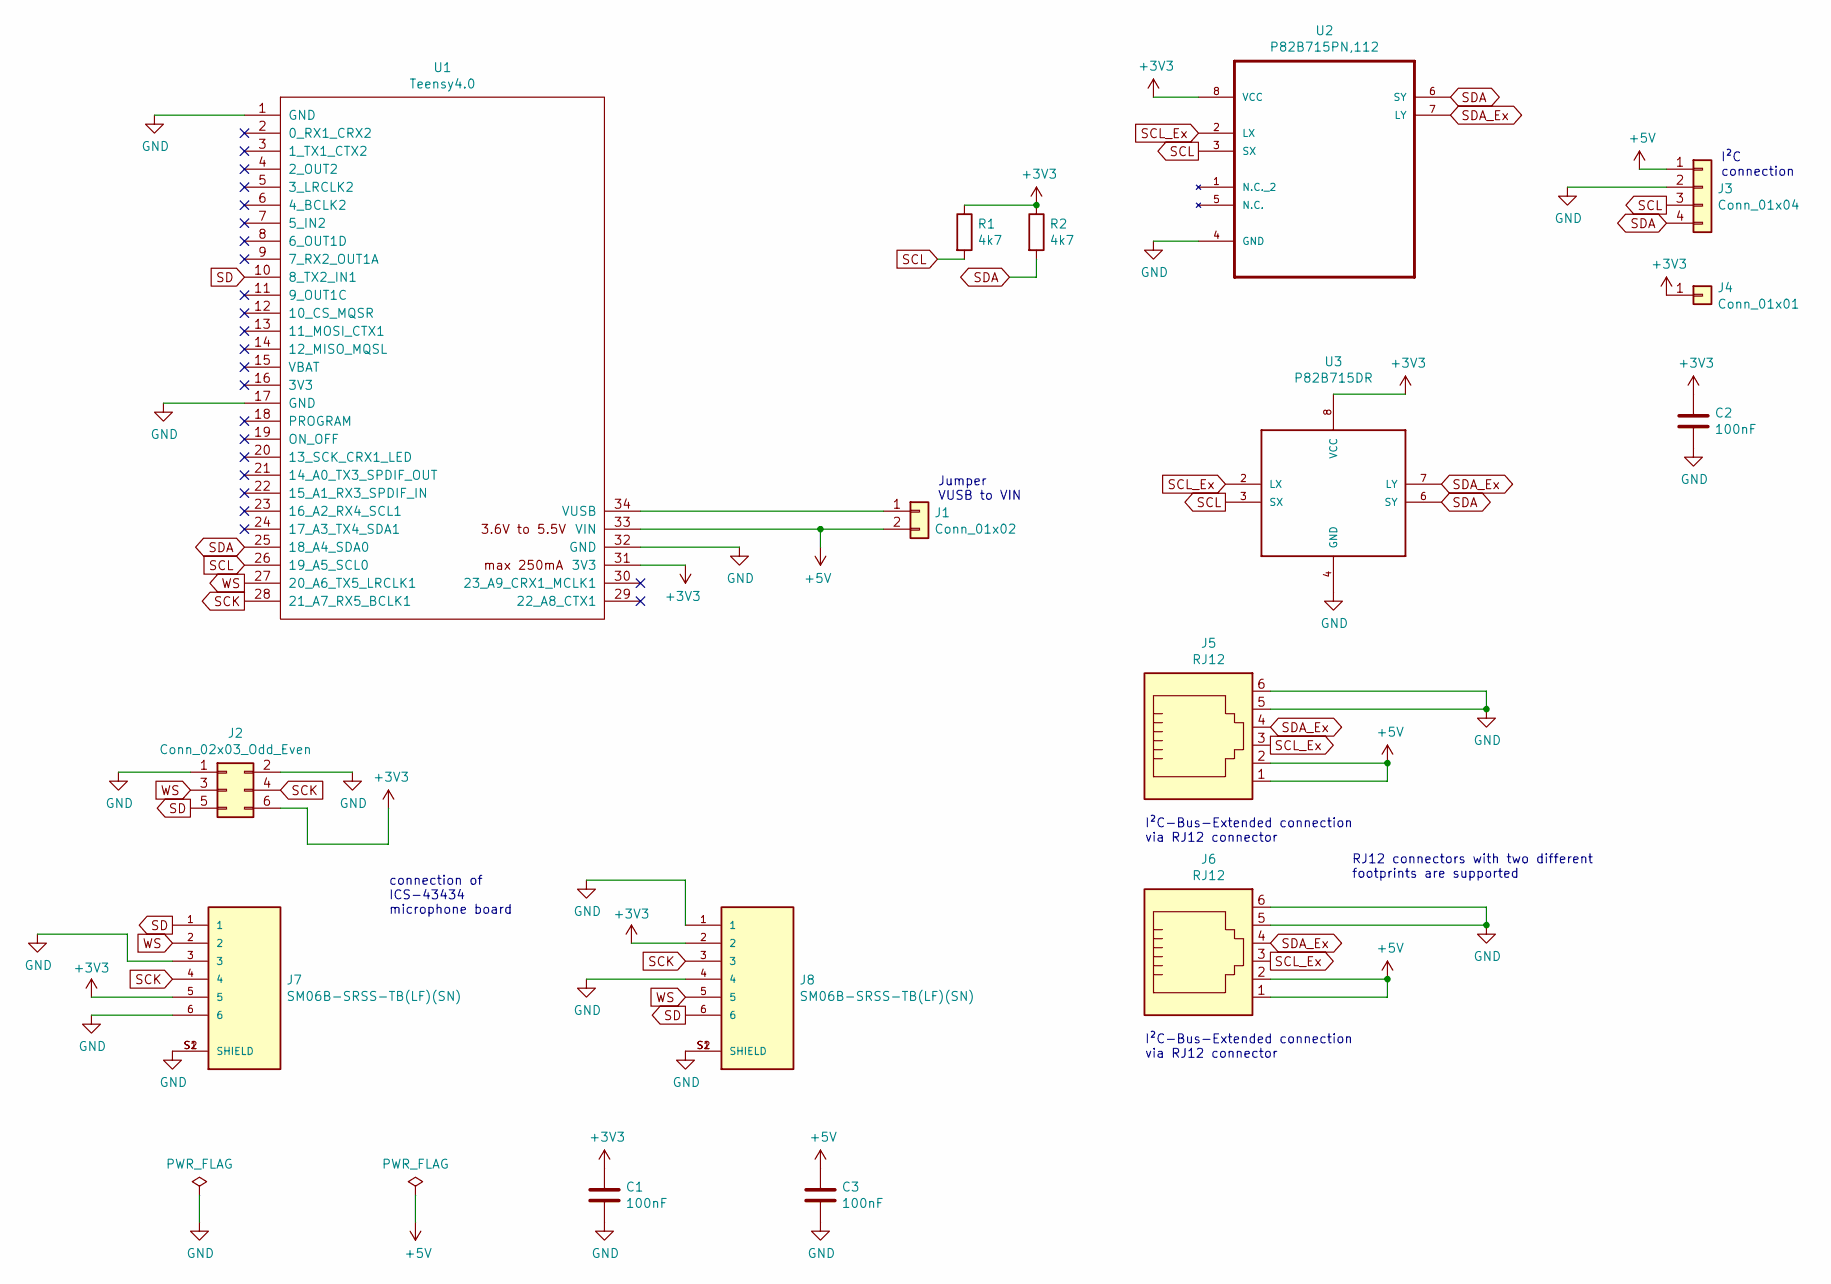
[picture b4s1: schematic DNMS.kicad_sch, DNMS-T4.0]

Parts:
C1, C2, C3: 100nF; C_THT_100nF_L9.0mm_W2.0mm_P5.00mm_P7.50mm
J1: Conn_01x02; PinHeader_1x02_P2.54mm_Vertical
J2: Conn_02x03_Odd_Even; PinHeader_2x03_P2.54mm_Vertical
J3: Conn_01x04; PinHeader_1x04_P2.54mm_Vertical
J4: Conn_01x01; PinHeader_1x01_P2.54mm_Vertical
J5: RJ12; 54601906WPLF
J6: RJ12; E5566Q0LK22L
J7, J8: SM06B-SRSS-TB(LF)(SN); JST_SM06B-SRSS-TB(LF)(SN)
R1, R2: 4k7; R_Axial_DIN0207_L6.3mm_D2.5mm_P10.16mm_Horizontal
U1: Teensy4.0; Teensy40
U2: P82B715PN,112; DIP254P762X420-8
U3: P82B715DR; SOIC8

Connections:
+3V3: C1.1, C2.1, J2.6, J4.1, J7.5, J8.2, R1.1, R2.1, U1.31 (3V3), U2.8 (VCC), U3.8 (VCC)
+5V: C3.1, J1.2, J3.1, J5.1, J5.2, J6.1, J6.2, U1.33 (VIN)
GND: C1.2, C2.2, C3.2, J2.1, J2.2, J3.2, J5.5, J5.6, J6.5, J6.6, J7.3, J7.6, J7.S1 (SHIELD), J7.S2 (SHIELD), J8.1, J8.4, J8.S1 (SHIELD), J8.S2 (SHIELD), U1.1 (GND), U1.17 (GND), U1.32 (GND), U2.4 (GND), U3.4 (GND)
unnamed: J1.1, U1.34 (VUSB)
SCK: J2.4, J7.4, J8.3, U1.28 (21_A7_RX5_BCLK1)
SCL: J3.3, R1.2, U1.26 (19_A5_SCL0), U2.3 (SX), U3.3 (SX)
SCL_Ex: J5.3, J6.3, U2.2 (LX), U3.2 (LX)
SD: J2.5, J7.1, J8.6, U1.10 (8_TX2_IN1)
SDA: J3.4, R2.2, U1.25 (18_A4_SDA0), U2.6 (SY), U3.6 (SY)
SDA_Ex: J5.4, J6.4, U2.7 (LY), U3.7 (LY)
WS: J2.3, J7.2, J8.5, U1.27 (20_A6_TX5_LRCLK1)

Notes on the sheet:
I²C-Bus-Extended connection via RJ12 connector
RJ12 connectors with two different footprints are supported
Jumper VUSB to VIN
connection of ICS-43434 microphone board
I²C connection

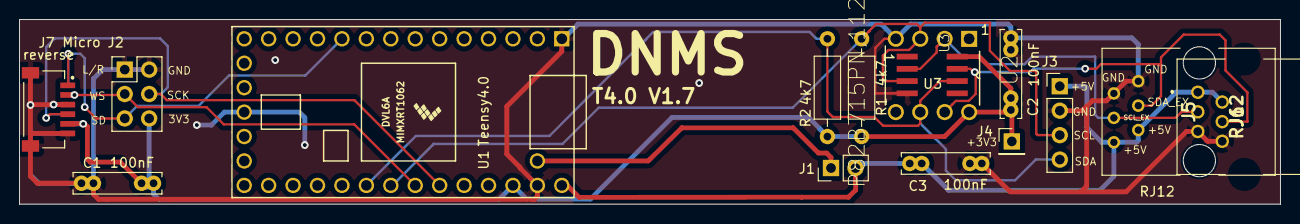
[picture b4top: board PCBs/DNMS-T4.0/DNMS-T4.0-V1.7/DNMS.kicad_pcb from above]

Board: 2 copper layers, 131.1 x 19.2 mm, 16 parts (1 on the bottom side), 11 nets.

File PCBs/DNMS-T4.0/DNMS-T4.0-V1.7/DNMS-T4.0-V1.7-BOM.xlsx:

BOM | DNMS-T4.0-V1.7
Item # | Reference | Qty | Manufacturer | Manufacturer Part # | Description / Value | Package/Footprint | Type | Distributor | Distributor # | Link to Distributor | Link to alternate Source | Link to alternate Source | Notes
1 | C1, C2, C3 | 3 | Vishay | K104K15X7RF53H5L | Multilayer Ceramic Capacitors MLCC - Leaded 0.1uF 50volts 10% X7R 5mm LS | 5mm LS | THT | Mouser | 594-K104K15X7RF53H5 | Mouser | Reichelt | Voelkner | any other Manufacturer is ok
2 | J1 | 1 | Amphenol FCI | 10129378-902001BLF | PIN Header 1x02 P2.54mm vertical | P2.54mm | THT | Mouser | 649-1012937890201BLF | Mouser | Reichelt | Voelkner | any other Manufacturer is ok
3 | J2 | 1 | Würth | 61200621721 | Sockel & Kabelgehäuse WR-BHD 2.54mm Male 6P Angl Gold BoX Hdr | P2.54mm 2x3 | THT | Mouser | 710-61200621721 | Mouser | Reichelt | Voelkner | either J2, J7 or J8 for connection to microphone. J7 or J8 is for cable with JS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
4 | J3 | 1 | Amphenol Commercial Products | G800W304018EU | Pin Header 2.54mm Pitch STR DIP,1x4Pin,FULL G/F,NY6T,6.1mm*2.5mm*3.0mm,Color-Bl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 | P2,54mm | THT | Mouser | 523-G800W304018EU | Mouser | Reichelt | Voelkner | any other Manufacturer is ok, (optional)
5 | J4 | 1 | Samtec | TSW-101-07-T-S | PIN Header 1x01 P2.54mm vertical | P2,54mm | THT | Mouser | 200-TSW10107TS | Mouser | Reichelt |  | any other Manufacturer is ok, (optional)
6 | J5 | 1 | Amphenol FCI | 54601-906WPLF | MOD JACK RJ12 6P6C CAT 3 HORIZ. 1 PORT |  | THT | Mouser | 649-54601-906WPLF | Mouser |  |  | either J5 or J6 as alternate assembly, this is the preferred assembly because o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
7 | J6 | 1 | Pulse Electronics | E5566-Q0LK22-L | Modular Jack RJ12/RJ25 6P6C SIDE ENTRY |  | THT | Mouser | 673-E5566-Q0LK22-L | Mouser | Reichelt | Voelkner | either J5 or J6 as alternate assembly, any other Manufacturer is ok
 | J7 | 1 | JST | SM06B-SRSS-TB (LF)(SN) | SR /SZ CONNECTOR 1.0mm pitch/Disconnectable Insulation displacement connectors |  | SMD | Voelkner | W581121 | Voelkner |  |  | either J2, J7 or J8 for connection to microphone. J7 or J8 is for cable with JS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
 | J8 | 1 | JST | SM06B-SRSS-TB (LF)(SN) | SR /SZ CONNECTOR 1.0mm pitch/Disconnectable Insulation displacement connectors |  | SMD | Voelkner | W581121 | Voelkner |  |  | either J2, J7 or J8 for connection to microphone. J7 or J8 is for cable with JS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
8 | R1, R2 | 2 | Vishay | CCF074K70JKE36 | Metal Film Resistor 1/4watt 4.7Kohms 5% Rated to 1/2watt | 6,62mm axial | THT | Mouser | 71-CCF07-J-4.7K-E3 | Mouser | Reichelt | Voelkner | any other Manufacturer is ok, Kohleschicht oder Metallschicht, 0,25Watt oder 0,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
9 | U1 | 1 | PJRC | TEENSY40 | Teensy 4.0 Development Board | 1.4 by 0.7 inch | THT | Antratek Electronics Deutschland | TEENSY40 | Antratek Electronics Deutschland | EXP GmbH
10 | U2 | 1 | Texas Instruments | P82B715P | Signal Buffer, Verstärker I2C Bus Extender | DIP8 | THT | Mouser | 595-P82B715P | Mouser |  |  | either U2 or U3 as alternate assembly, any other Manufacturer is ok
11 | U3 | 1 | Texas Instruments | P82B715DR | Signal Buffer, Verstärker I2C Bus Extender | SOIC8 | SMD | Mouser | 595-P82B715DR | Mouser | Reichelt |  | either U2 or U3 as alternate assembly, any other Manufacturer is ok

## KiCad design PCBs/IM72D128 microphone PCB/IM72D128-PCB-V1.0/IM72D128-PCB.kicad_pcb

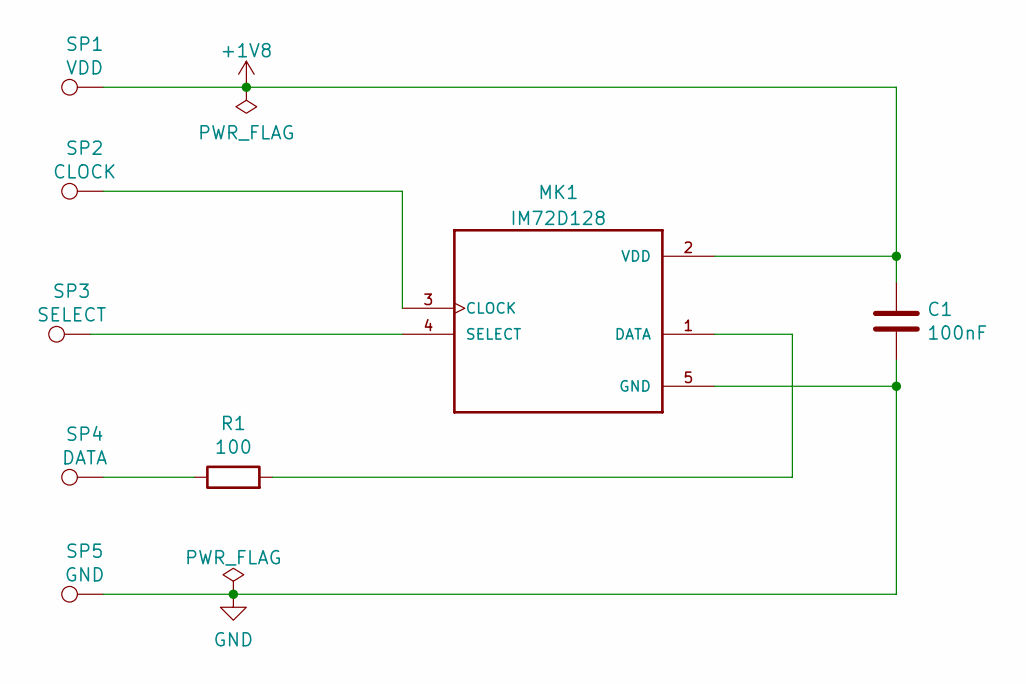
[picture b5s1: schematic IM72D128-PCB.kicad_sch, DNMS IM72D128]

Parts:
C1: 100nF; C_0603_1608Metric
MK1: IM72D128; MIC_IM72D128
R1: 100; R_0603_1608Metric
SP1: VDD; Solder_Pad_1.0x1.0mm
SP2: CLOCK; Solder_Pad_1.0x1.0mm
SP3: SELECT; Solder_Pad_1.0x1.0mm
SP4: DATA; Solder_Pad_1.0x1.0mm
SP5: GND; Solder_Pad_1.0x1.0mm

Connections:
+1V8: C1.1, MK1.2 (VDD), SP1.1
GND: C1.2, MK1.5 (GND), SP5.1
unnamed: MK1.3 (CLOCK), SP2.1
unnamed: MK1.1 (DATA), R1.2
unnamed: MK1.4 (SELECT), SP3.1
unnamed: R1.1, SP4.1

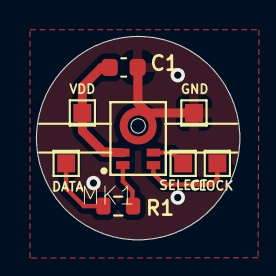
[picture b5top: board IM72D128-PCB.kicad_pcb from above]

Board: 2 copper layers, 11.3 x 11.3 mm, 8 parts (0 on the bottom side), 6 nets.
